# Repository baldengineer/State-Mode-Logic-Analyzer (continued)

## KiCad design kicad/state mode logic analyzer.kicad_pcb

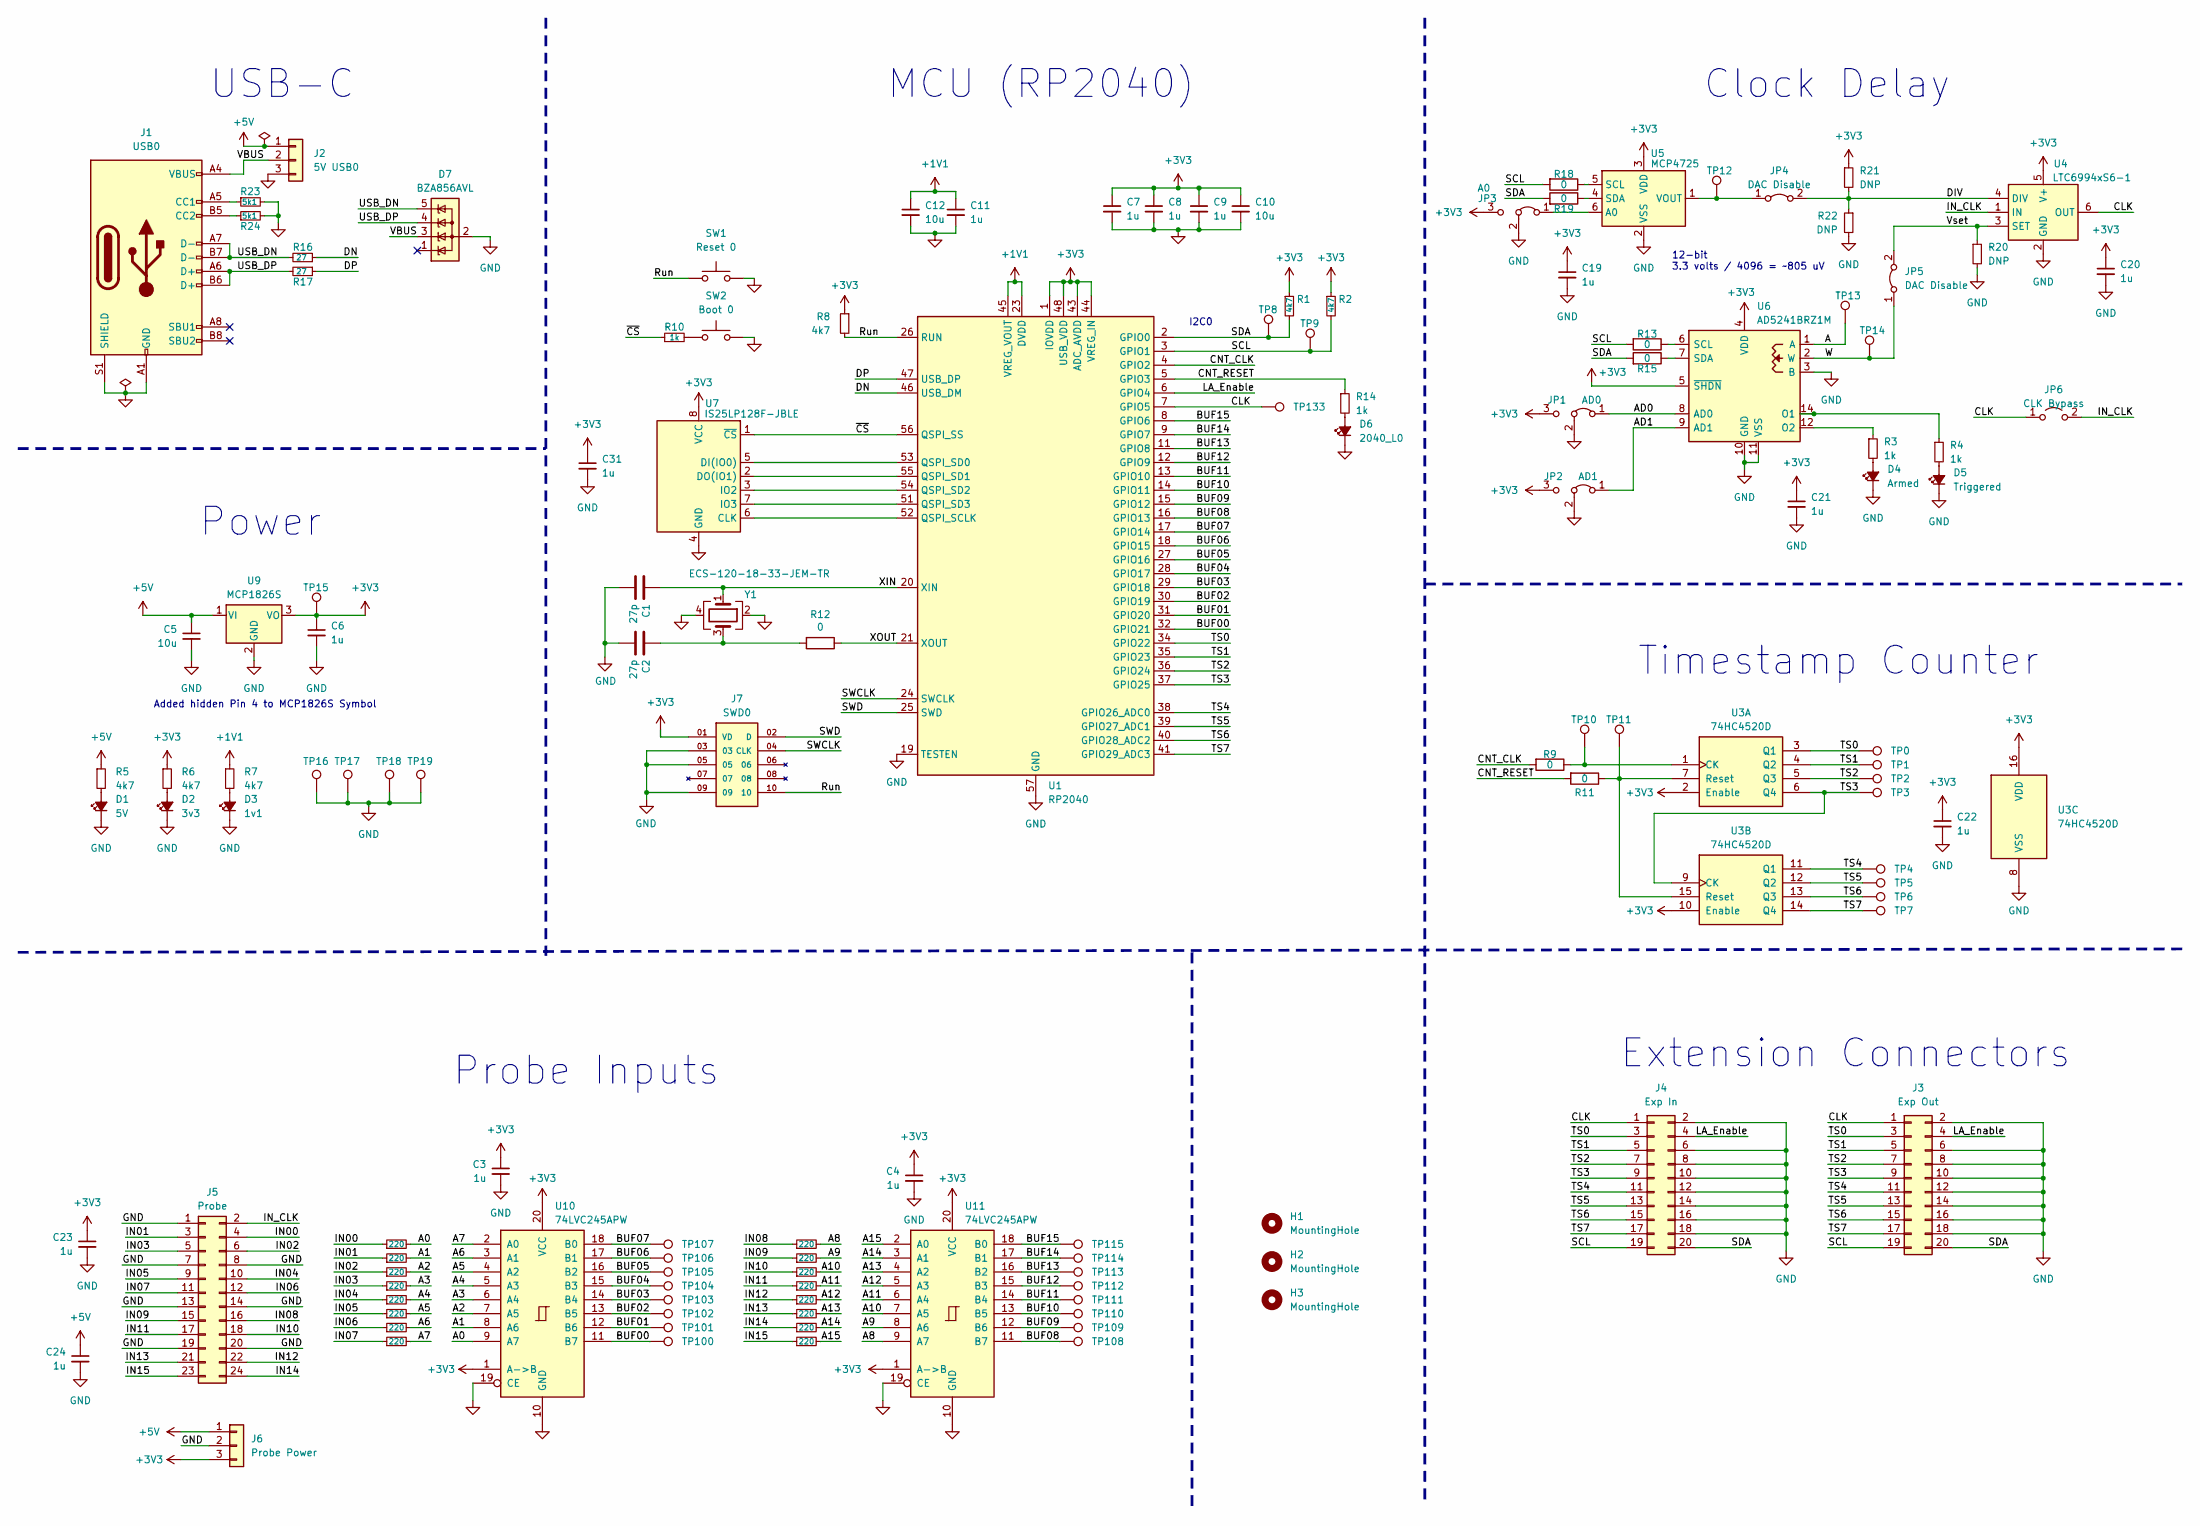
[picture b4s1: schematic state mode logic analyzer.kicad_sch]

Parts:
C1, C2: 27p; C_0603_1608Metric
C3, C4, C7, C8, C9, C11, C19, C20, C21, C22, C23, C24, C31: 1u; C_0603_1608Metric_Pad1.08x0.95mm_HandSolder
C5, C10, C12: 10u; C_0805_2012Metric
C6: 1u; C_0805_2012Metric
D1: 5V; LED_1206_3216Metric_Pad1.42x1.75mm_HandSolder
D2: 3v3; LED_1206_3216Metric_Pad1.42x1.75mm_HandSolder
D3: 1v1; LED_1206_3216Metric_Pad1.42x1.75mm_HandSolder
D4: Armed; LED_1206_3216Metric_Pad1.42x1.75mm_HandSolder
D5: Triggered; LED_1206_3216Metric_Pad1.42x1.75mm_HandSolder
D6: 2040_L0; LED_1206_3216Metric_Pad1.42x1.75mm_HandSolder
D7: BZA856AVL; SOT-353_SC-70-5
H1, H2, H3: MountingHole; MountingHole_2.7mm
J1: USB0; USB_C_Receptacle_GCT_USB4105-xx-A_16P_TopMnt_Horizontal
J2: 5V USB0; PinHeader_1x03_P2.54mm_Vertical
J3: Exp Out; PinHeader_2x10_P2.54mm_Horizontal
J4: Exp In; PinSocket_2x10_P2.54mm_Horizontal
J5: Probe; PinHeader_2x12_P2.54mm_Vertical
J6: Probe Power; PinHeader_1x03_P2.54mm_Vertical
J7: SWD0; SAMTEC_FTSH-105-XX-X-DV; PARTREV H
JP1: AD0; SolderJumper-3_P1.3mm_Bridged2Bar12_Pad1.0x1.5mm
JP2: AD1; SolderJumper-3_P1.3mm_Bridged2Bar12_Pad1.0x1.5mm
JP3: A0; SolderJumper-3_P1.3mm_Bridged2Bar12_Pad1.0x1.5mm
JP4, JP5: DAC Disable; SolderJumper-2_P1.3mm_Bridged2Bar_Pad1.0x1.5mm
JP6: CLK Bypass; SolderJumper-2_P1.3mm_Open_Pad1.0x1.5mm
R1, R2, R5, R6, R7, R8: 4k7; R_0603_1608Metric_Pad0.98x0.95mm_HandSolder
R3, R4, R10, R14: 1k; R_0603_1608Metric_Pad0.98x0.95mm_HandSolder
R9, R11, R12, R13, R15, R18, R19: 0; R_0603_1608Metric_Pad0.98x0.95mm_HandSolder
R16, R17: 27; R_0603_1608Metric_Pad0.98x0.95mm_HandSolder
R20, R21, R22: DNP; R_0603_1608Metric_Pad0.98x0.95mm_HandSolder
R23, R24: 5k1; R_0603_1608Metric_Pad0.98x0.95mm_HandSolder
R25, R26, R27, R28, R29, R30, R31, R32, R33, R34, R35, R36, R37, R38, R39, R40: 220; R_0603_1608Metric
SW1: Reset 0; SW_SPST_PTS810
SW2: Boot 0; SW_SPST_PTS810
TP0, TP1, TP2, TP3, TP4, TP5, TP6, TP7, TP8, TP9, TP10, TP11, TP12, TP13, TP14, TP15, TP16, TP17, TP18, TP19, TP100, TP101, TP102, TP103, TP104, TP105, TP106, TP107, TP108, TP109, TP110, TP111, TP112, TP113, TP114, TP115, TP133: TestPoint_Harwin; Harwin-S1751-46-Test-Point
U1: RP2040; QFN-56-1EP_7x7mm_P0.4mm_EP3.2x3.2mm
U3: 74HC4520D; TSSOP-16_4.4x5mm_P0.65mm
U4: LTC6994xS6-1; TSOT-23-6
U5: MCP4725; SOT-23-6
U6: AD5241BRZ1M; SOIC-14_3.9x8.7mm_P1.27mm
U7: IS25LP128F-JBLE; SOIC-8_5.23x5.23mm_P1.27mm
U9: MCP1826S; SOT-223
U10, U11: 74LVC245APW; TSSOP-20_4.4x6.5mm_P0.65mm
Y1: ECS-120-18-33-JEM-TR; Crystal_SMD_3225-4Pin_3.2x2.5mm

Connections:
+1V1: C11.1, C12.1, R7.1, U1.23 (DVDD), U1.45 (VREG_VOUT), U1.50 (DVDD)
+3V3: C3.1, C4.1, C6.1, C7.1, C8.1, C9.1, C10.1, C19.1, C20.1, C21.1, C22.1, C23.1, C31.1, J6.3, J7.01 (VD), JP1.3 (B), JP2.3 (B), JP3.3 (B), R1.1, R2.1, R6.1, R8.1, R21.1, TP15.1, U1.1 (IOVDD), U1.10 (IOVDD), U1.22 (IOVDD), U1.33 (IOVDD), U1.42 (IOVDD), U1.43 (ADC_AVDD), U1.44 (VREG_IN), U1.48 (USB_VDD), U1.49 (IOVDD), U3.2 (Enable), U3.10 (Enable), U3.16 (VDD), U4.5 (V+), U5.3 (VDD), U6.4 (VDD), U6.5 (~SHDN), U7.8 (VCC), U9.3 (VO), U10.1 (A->B), U10.20 (VCC), U11.1 (A->B), U11.20 (VCC)
+5V: C5.1, C24.1, J2.1, J6.1, R5.1, U9.1 (VI)
/A: TP13.1, U6.1 (A)
/A0: R25.2, U10.9 (A7)
/A1: R26.2, U10.8 (A6)
/A2: R27.2, U10.7 (A5)
/A3: R28.2, U10.6 (A4)
/A4: R29.2, U10.5 (A3)
/A5: R30.2, U10.4 (A2)
/A6: R31.2, U10.3 (A1)
/A7: R32.2, U10.2 (A0)
/A8: R33.2, U11.9 (A7)
/A9: R34.2, U11.8 (A6)
/A10: R35.2, U11.7 (A5)
/A11: R36.2, U11.6 (A4)
/A12: R37.2, U11.5 (A3)
/A13: R38.2, U11.4 (A2)
/A14: R39.2, U11.3 (A1)
/A15: R40.2, U11.2 (A0)
/AD0: JP1.1 (A), U6.8 (AD0)
/AD1: JP2.1 (A), U6.9 (AD1)
/BUF00: TP100.1, U1.32 (GPIO21), U10.11 (B7)
/BUF01: TP101.1, U1.31 (GPIO20), U10.12 (B6)
/BUF02: TP102.1, U1.30 (GPIO19), U10.13 (B5)
/BUF03: TP103.1, U1.29 (GPIO18), U10.14 (B4)
/BUF04: TP104.1, U1.28 (GPIO17), U10.15 (B3)
/BUF05: TP105.1, U1.27 (GPIO16), U10.16 (B2)
/BUF06: TP106.1, U1.18 (GPIO15), U10.17 (B1)
/BUF07: TP107.1, U1.17 (GPIO14), U10.18 (B0)
/BUF08: TP108.1, U1.16 (GPIO13), U11.11 (B7)
/BUF09: TP109.1, U1.15 (GPIO12), U11.12 (B6)
/BUF10: TP110.1, U1.14 (GPIO11), U11.13 (B5)
/BUF11: TP111.1, U1.13 (GPIO10), U11.14 (B4)
/BUF12: TP112.1, U1.12 (GPIO9), U11.15 (B3)
/BUF13: TP113.1, U1.11 (GPIO8), U11.16 (B2)
/BUF14: TP114.1, U1.9 (GPIO7), U11.17 (B1)
/BUF15: TP115.1, U1.8 (GPIO6), U11.18 (B0)
/CLK: J3.1, J4.1, JP6.1 (A), TP133.1, U1.7 (GPIO5), U4.6 (OUT)
/CNT_CLK: R9.2, U1.4 (GPIO2)
/CNT_RESET: R11.2, R14.1, U1.5 (GPIO3)
/DIV: JP4.2 (B), R21.2, R22.1, U4.4 (DIV)
/DN: R16.1, U1.46 (USB_DM)
/DP: R17.1, U1.47 (USB_DP)
/IN00: J5.4, R25.1
/IN01: J5.3, R26.1
/IN02: J5.6, R27.1
/IN03: J5.5, R28.1
/IN04: J5.10, R29.1
/IN05: J5.9, R30.1
/IN06: J5.12, R31.1
/IN07: J5.11, R32.1
/IN08: J5.16, R33.1
/IN09: J5.15, R34.1
/IN10: J5.18, R35.1
/IN11: J5.17, R36.1
/IN12: J5.22, R37.1
/IN13: J5.21, R38.1
/IN14: J5.24, R39.1
/IN15: J5.23, R40.1
/IN_CLK: J5.2, JP6.2 (B), U4.1 (IN)
/LA_Enable: J3.4, J4.4, U1.6 (GPIO4)
/Run: J7.10, R8.2, SW1.1, U1.26 (RUN)
/SCL: J3.19, J4.19, R2.2, R13.2, R18.2, TP9.1, U1.3 (GPIO1)
/SDA: J3.20, J4.20, R1.2, R15.2, R19.2, TP8.1, U1.2 (GPIO0)
/SWCLK: J7.04 (CLK), U1.24 (SWCLK)
/SWD: J7.02 (D), U1.25 (SWD)
/TS0: J3.3, J4.3, TP0.1, U1.34 (GPIO22), U3.3 (Q1)
/TS1: J3.5, J4.5, TP1.1, U1.35 (GPIO23), U3.4 (Q2)
/TS2: J3.7, J4.7, TP2.1, U1.36 (GPIO24), U3.5 (Q3)
/TS3: J3.9, J4.9, TP3.1, U1.37 (GPIO25), U3.6 (Q4), U3.9 (CK)
/TS4: J3.11, J4.11, TP4.1, U1.38 (GPIO26_ADC0), U3.11 (Q1)
/TS5: J3.13, J4.13, TP5.1, U1.39 (GPIO27_ADC1), U3.12 (Q2)
/TS6: J3.15, J4.15, TP6.1, U1.40 (GPIO28_ADC2), U3.13 (Q3)
/TS7: J3.17, J4.17, TP7.1, U1.41 (GPIO29_ADC3), U3.14 (Q4)
/USB_DN: D7.5 (K), J1.A7 (D-), J1.B7 (D-), R16.2
/USB_DP: D7.4 (K), J1.A6 (D+), J1.B6 (D+), R17.2
/VBUS: D7.3 (K), J1.A4 (VBUS), J1.A9 (VBUS), J1.B4 (VBUS), J1.B9 (VBUS), J2.2
/Vset: JP5.2 (B), R20.1, U4.3 (SET)
/W: JP5.1 (A), TP14.1, U6.2 (W)
/XIN: C1.1, U1.20 (XIN), Y1.1
/XOUT: R12.1, U1.21 (XOUT)
/~CS: R10.1, U1.56 (QSPI_SS), U7.1 (~CS)
GND: C1.2, C2.2, C3.2, C4.2, C5.2, C6.2, C7.2, C8.2, C9.2, C10.2, C11.2, C12.2, C19.2, C20.2, C21.2, C22.2, C23.2, C24.2, C31.2, D1.1 (K), D2.1 (K), D3.1 (K), D4.1 (K), D5.1 (K), D6.1 (K), D7.2 (A), J1.A1 (GND), J1.A12 (GND), J1.B1 (GND), J1.B12 (GND), J1.S1 (SHIELD), J2.3, J3.2, J3.6, J3.8, J3.10, J3.12, J3.14, J3.16, J3.18, J4.2, J4.6, J4.8, J4.10, J4.12, J4.14, J4.16, J4.18, J5.1, J5.7, J5.8, J5.13, J5.14, J5.19, J5.20, J6.2, J7.03, J7.05, J7.09, JP1.2 (C), JP2.2 (C), JP3.2 (C), R20.2, R22.2, R23.2, R24.2, SW1.2, SW2.2, TP16.1, TP17.1, TP18.1, TP19.1, U1.19 (TESTEN), U1.57 (GND), U3.8 (VSS), U4.2 (GND), U5.2 (VSS), U6.3 (B), U6.10 (GND), U6.11 (VSS), U7.4 (GND), U9.2 (GND), U9.4 (GND), U10.10 (GND), U10.19 (CE), U11.10 (GND), U11.19 (CE), Y1.2, Y1.4
unnamed: C2.1, R12.2, Y1.3
unnamed: D1.2 (A), R5.2
unnamed: D2.2 (A), R6.2
unnamed: D3.2 (A), R7.2
unnamed: D4.2 (A), R3.2
unnamed: D5.2 (A), R4.2
unnamed: D6.2 (A), R14.2
unnamed: J1.A5 (CC1), R23.1
unnamed: J1.B5 (CC2), R24.1
unnamed: JP3.1 (A), U5.6 (A0)
unnamed: JP4.1 (A), TP12.1, U5.1 (VOUT)
unnamed: R10.2, SW2.1
unnamed: U1.52 (QSPI_SCLK), U7.6 (CLK)
unnamed: U1.53 (QSPI_SD0), U7.5 (DI(IO0))
unnamed: U1.55 (QSPI_SD1), U7.2 (DO(IO1))
unnamed: U1.54 (QSPI_SD2), U7.3 (IO2)
unnamed: U1.51 (QSPI_SD3), U7.7 (IO3)
unnamed: R9.1, TP10.1, U3.1 (CK)
unnamed: R11.1, TP11.1, U3.7 (Reset), U3.15 (Reset)
unnamed: R18.1, U5.5 (SCL)
unnamed: R19.1, U5.4 (SDA)
unnamed: R4.1, U6.14 (O1)
unnamed: R3.1, U6.12 (O2)
unnamed: R13.1, U6.6 (SCL)
unnamed: R15.1, U6.7 (SDA)

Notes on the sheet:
I2C0
Extension Connectors
Clock Delay
Timestamp Counter
Added hidden Pin 4 to MCP1826S Symbol
Power
USB-C
MCU (RP2040)
12-bit 3.3 volts / 4096 = ~805 uV
Probe Inputs

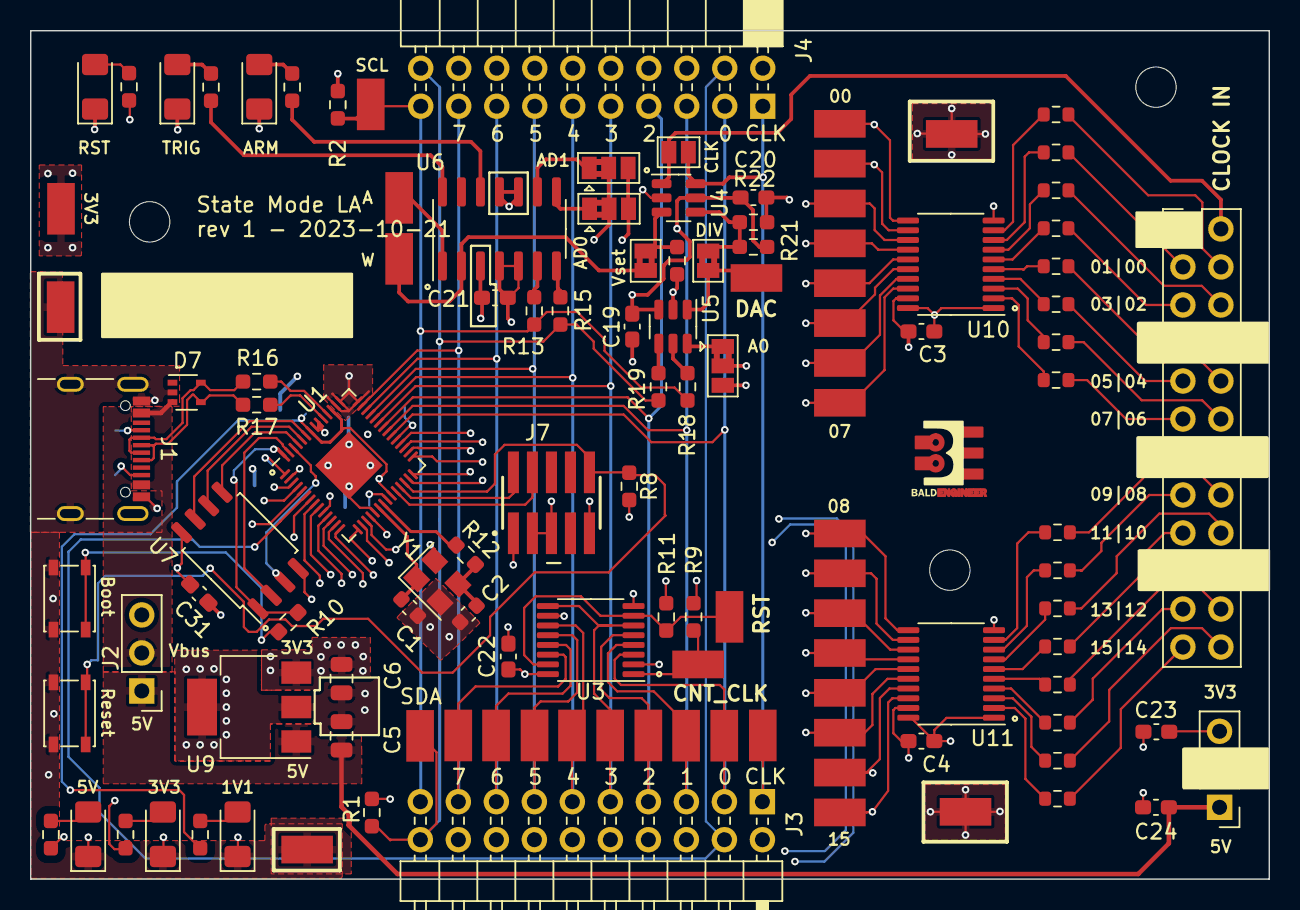
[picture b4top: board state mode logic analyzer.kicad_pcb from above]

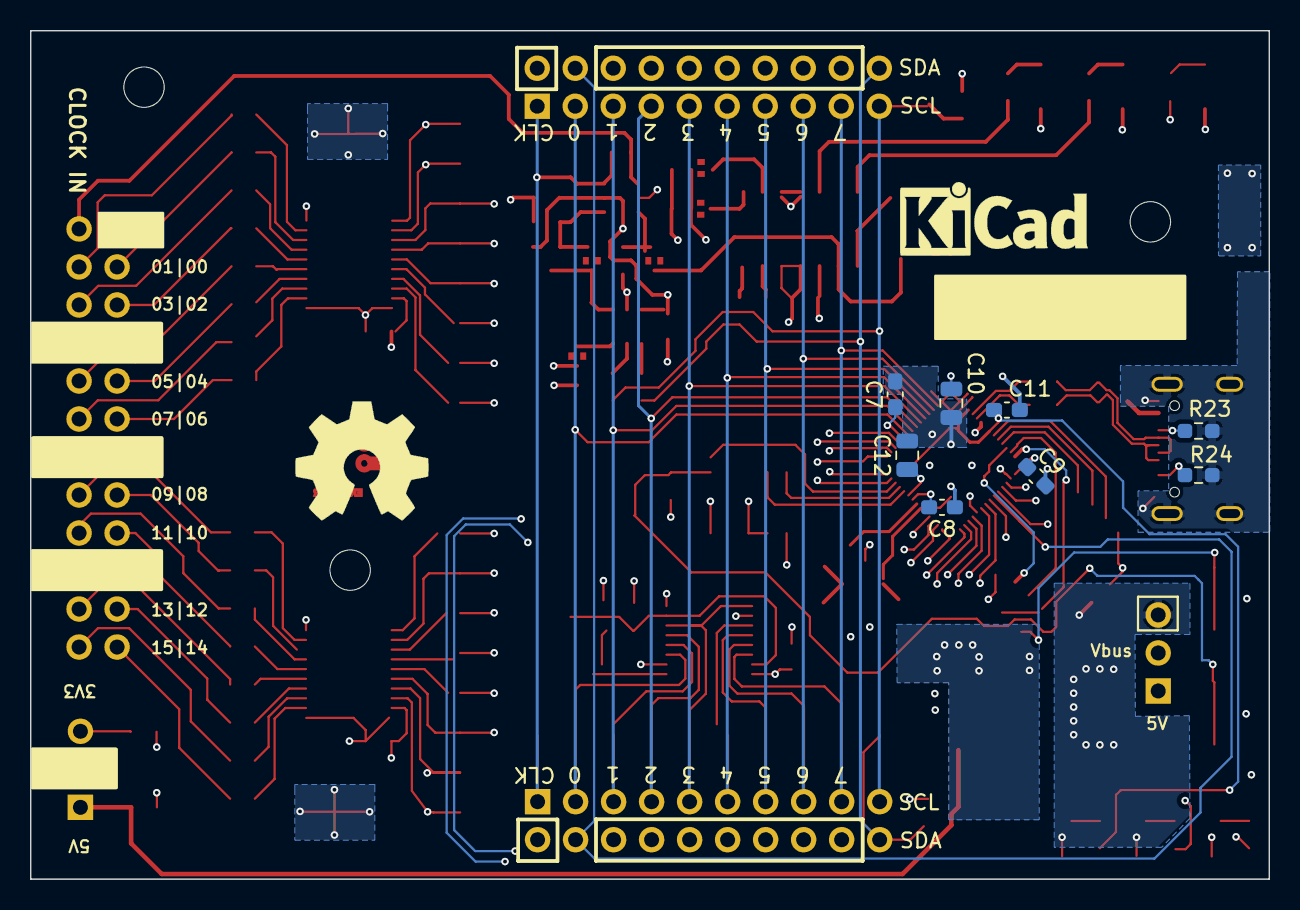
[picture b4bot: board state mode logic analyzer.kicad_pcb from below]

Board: 4 copper layers, 82.8 x 56.7 mm, 132 parts (8 on the bottom side), 109 nets.

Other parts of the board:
svg2mod: G***; BE5v2

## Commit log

2023-10-20 initial schematic layout before ERC
2023-10-20 switched to usb-c
2023-10-20 passed erc for first schem ver
2023-10-20 initial pcb plop
2023-10-20 saving current state to try a different design
2023-10-21 floor planning ongoing
2023-10-21 going to re-order all the IOs
2023-10-21 passed drc and started silk clean up
2023-10-22 rev1 before verification
2023-10-22 rneed to review again
2023-10-22 Deocrated schematic
2023-10-22 gerbers plotted for fab
2023-10-22 added distributor part numbers
2023-10-22 fixed J desgs and swapped prog header part num
2023-10-22 pdf update only for rev1 submit
2023-11-10 initial pico test code
2023-11-10 setup PIO, DMA, and Serial. Untested
2023-11-15 pico sampling 8 bits seemingly correct
2023-11-15 Fixed encode_jmp bug with origin addr
2023-11-16 changed clk_in to match PCB
2023-11-18 pwm clock gen
2023-11-20 i2c scan from examples and pwm code on final board
2024-08-22 starting over
2024-08-22 moving stuff around
2024-08-23 fixing ERC errors
2024-08-23 end of stream commit
2024-08-31 tried doing clkdly in the pio and it was sucecssful
2024-08-31 removed clock delay and timestamp counter since it can be done in pio.
2024-08-31 rp2040 pio clock delay and pio counter (timestamp) example / initial work
2024-08-31 moved tstamp to pio0
2024-08-31 added wait for usb and some code cleanup
2024-09-01 taking AD2 Waveforms files out of git
2024-09-01 some systick stuff, may delete later
2024-09-02 pio irq crashing
2024-09-02 isr runs once but pio seems to lock up
2024-09-02 pushing value back into pio0 fifo works...
2024-09-02 have to reset FIFO in ISR
2024-09-02 going in the wrong direction need to share pin for flag and dma buffers
2024-09-02 wroks as expected but is too slow
2024-09-13 moved to 2-supply buffer design
2024-10-10 rough layout check going to re do it for real
2024-10-10 replaced discrete rp2350 with stampxl (schematic only)
2024-10-11 remove complicated Vccb supply circuit
2024-10-11 drc after adding in Buffered DAC
2024-10-11 moving from schematic to pcb
2024-10-11 early pcb layout - need to build a demo/test board next
2024-10-11 initial dac commit
2024-10-11 schematic passes erc
2024-10-12 pcb initial layout
2024-11-10 added stemma, decoupling caps for buffers -- forgot i was going to start making the dac test board
2024-11-10 changed In pinout to put GND in middle and added stemma qt
2024-11-10 added osh 4-layer rules
2024-11-10 forgot the ldo... :(
2024-11-10 splitting project
2024-11-10 initial rip-up for dac only
2024-11-10 pcb passes drc
2024-11-11 buffer breakout initial create
2024-11-11 renamed files, was working on wrong directory
2024-11-11 floor planning attempt 1
2024-11-11 drc passed rev1
2024-11-11 rev1 gerbs and pdfs
2024-11-11 added rev 1 breakout images
2024-11-11 cleaning up gitignore
2024-11-11 generated BOMs for breakouts
2024-11-11 hiding lock files
2024-11-12 ignore 7z
2024-11-12 updated buffer PNs and reordered pins to match XL pinout
2024-11-12 replaces term resistors with arrays
